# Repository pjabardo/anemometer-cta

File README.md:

# Project of a thermistor based constant temperature anemometer

This repository contains files related to a constant temperature anemometer that uses a self heated NTC thermistor as a sensing element.

## Thermal anemometer

An anemometer is a device that measures fluid speed, in particular air. A thermal anemometer uses heat transfer from a heated element to estimate the velocity of the fluid. There are several ways to build a thermal anemometer but the most common is the use of a self heated resistor whose resistance varies with temperature.

As a side note, a few years ago, José Pucci Caly, a professor at Mackenzie University in São Paulo/Brazil developed with a couple of students a very simple anemometer: the external temperature of the bulb from an incandescent light bulb was calibrated against wind speed. It worked. How well? I don't remember...

There are several ways that a self heated resistor can be used as the two mosto common aproaches are:

 * Constant temperature
 * Constant current

In this project we use the constant temperature approach.

## CTA - Constant temperature anemometer

The basic idea behind the constant temperature anemometer (CTA) is that an electric current passing through a resistor will heat the resistor. The temperature of the resistor is the result of the heat transfer to the fluid flowing around it.

Now suppose that for a given fluid velocity the temperature of the resistor is Tw. If the velocity then increases a tiny bit, Tw should drop a little bit. This drop in temperature corresponds to a change in resistance (when the resistance depends on the temperature). This change in resistance can be picked up and the current flowing through the resistor is changed accordingly.

The figure below shows the basic idea behind the anemometer. In this figure, Rw is the sensor. An imbalance of the Wheatsone bridge will cause a change of the current on the feedback loop. While this basic layout explains in general terms what is being done, it doesn't work. For one, most op amps can not provide sufficient current to the bridge. But there are other issues with this simple scheme.

This project uses an NTC thermistor (<https://en.wikipedia.org/wiki/Thermistor>) as a sensing element. In this case, an increase in temperature results in a decrease of resistance. This change can be drastic. For instance for a thermistor with a resistance of 5k at 25oC, at 180oC, the resistance can be 100 Ohms.

## Understanding the circuit

If the flow spead increases, the temperature will decrease and therefore the thermistor's resistance wqill increase and the voltage just before the sensor will increase and that will increase the output from the op amp so that it restores balance. To handle larger currents, the output of the op amp is connected to the base of an NPN transistor.

Even with the transistor in place, the circuit will not work. How does it start? When the power is turned on, there is no current on the bridge and therefore no imbalance and the base current is zero. So the circuit stays off indefinitely.

One possible solution is to nudge the + input of the op amp by connecting it to input voltage using a large resistor. This will work but now we have a problem: the operating point of the circuit will depend on the input voltage. This is not good. The figure below shows the basic circuit used:

This figure was generated from the text file  `cta-circuit.txt` using the online Falstad circuit simulator (<https://www.falstad.com/circuit/circuitjs.html>). Go to the previous link, select File -> Import from text and copy and paste the contents of the `cta-circuit.txt` file.

This is the completed circuit. The sub-circuit on the lower right hand side of the circuit basically unbalances the + input of op amp during power up so that the circuit is started. When the 10uF capacitor is charged, the PNP transistor is switched off and this branch of the circuit plays no role anymore.

There is now an input filter at the op amp. Without the feedback capacitor, once the bridge reached equilibrium, the current would be cutoff. The 100nF capacitor works as a integral controller.

The output of the anemometer is the voltage feeding the sensor. This output is fed to a voltage follower and then to a voltage divider to lower the voltage to levels adequate to an analog to digital converter and then there is another voltage follower to isolate the output.

This circuit uses 3 op amps and the LM324 quad 
## KiCad schematics

On the `kicad` folder is the KiCad project of the circuit.

## The finished board

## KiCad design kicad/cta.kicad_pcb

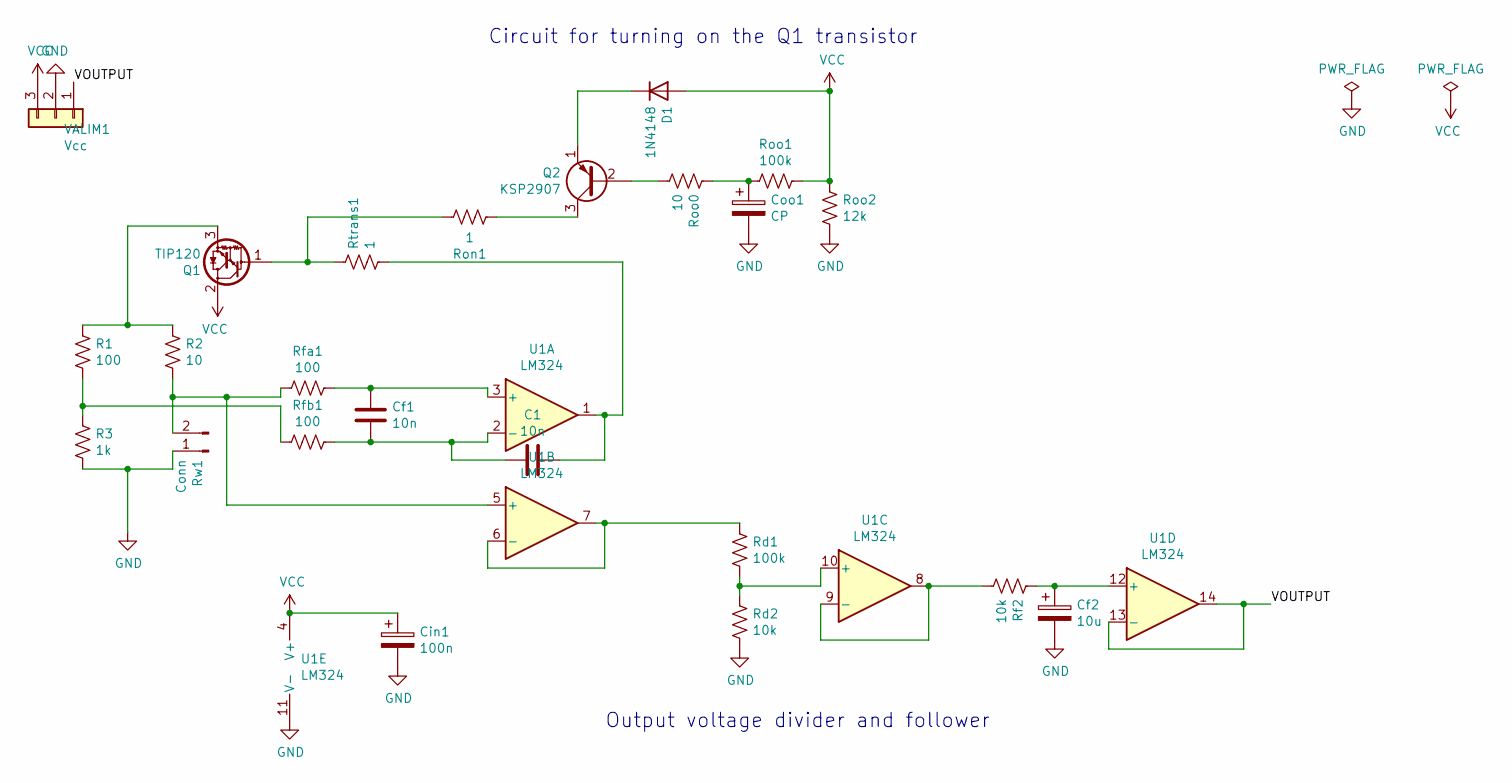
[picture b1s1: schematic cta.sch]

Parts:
C1: 10n; C_Rect_L7.2mm_W4.5mm_P5.00mm_FKS2_FKP2_MKS2_MKP2
Cf1: 10n; C_Rect_L7.2mm_W4.5mm_P5.00mm_FKS2_FKP2_MKS2_MKP2
Cf2: 10u; CP_Radial_D5.0mm_P2.50mm
Cin1: 100n; CP_Radial_D4.0mm_P2.00mm
Coo1: CP; CP_Radial_D5.0mm_P2.50mm
D1: 1N4148; D_DO-35_SOD27_P7.62mm_Horizontal
Q1: TIP120; TO-220-3_Vertical
Q2: KSP2907; TO-92_Inline_Wide
R1: 100; R_Axial_DIN0207_L6.3mm_D2.5mm_P10.16mm_Horizontal
R2: 10; R_Axial_Power_L20.0mm_W6.4mm_P22.40mm
R3: 1k; R_Axial_DIN0207_L6.3mm_D2.5mm_P10.16mm_Horizontal
Rd1: 100k; R_Axial_DIN0207_L6.3mm_D2.5mm_P10.16mm_Horizontal
Rd2: 10k; R_Axial_DIN0207_L6.3mm_D2.5mm_P10.16mm_Horizontal
Rf2: 10k; R_Axial_DIN0207_L6.3mm_D2.5mm_P10.16mm_Horizontal
Rfa1: 100; R_Axial_DIN0207_L6.3mm_D2.5mm_P10.16mm_Horizontal
Rfb1: 100; R_Axial_DIN0207_L6.3mm_D2.5mm_P10.16mm_Horizontal
Ron1: 1; R_Axial_DIN0207_L6.3mm_D2.5mm_P10.16mm_Horizontal
Roo0: 10; R_Axial_DIN0207_L6.3mm_D2.5mm_P10.16mm_Horizontal
Roo1: 100k; R_Axial_DIN0207_L6.3mm_D2.5mm_P10.16mm_Horizontal
Roo2: 12k; R_Axial_DIN0207_L6.3mm_D2.5mm_P10.16mm_Horizontal
Rtrans1: 1; R_Axial_DIN0207_L6.3mm_D2.5mm_P10.16mm_Horizontal
Rw1: Conn; TerminalBlock_bornier-2_P5.08mm
U1: LM324; DIP-14_W7.62mm_LongPads
VALIM1: Vcc; TerminalBlock_bornier-3_P5.08mm

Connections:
/VOUTPUT: U1.13 (-), U1.14, VALIM1.1
GND: Cf2.2, Cin1.2, Coo1.2, R3.2, Rd2.1, Roo2.2, Rw1.1, U1.11 (V-), VALIM1.2
unnamed: C1.1, Rtrans1.2, U1.1
unnamed: C1.2, Cf1.2, Rfb1.1, U1.2 (-)
unnamed: Cf1.1, Rfa1.1, U1.3 (+)
unnamed: Cf2.1, Rf2.1, U1.12 (+)
unnamed: Coo1.1, Roo0.1, Roo1.2
unnamed: D1.1 (K), Q2.1 (E)
unnamed: Q1.1 (B), Ron1.1, Rtrans1.1
unnamed: Q1.3 (E), R1.1, R2.1
unnamed: Q2.2 (B), Roo0.2
unnamed: Q2.3 (C), Ron1.2
unnamed: R1.2, R3.1, Rfb1.2
unnamed: R2.2, Rfa1.2, Rw1.2, U1.5 (+)
unnamed: Rd1.1, U1.6 (-), U1.7
unnamed: Rd1.2, Rd2.2, U1.10 (+)
unnamed: Rf2.2, U1.8, U1.9 (-)
VCC: Cin1.1, D1.2 (A), Q1.2 (C), Roo1.1, Roo2.1, U1.4 (V+), VALIM1.3

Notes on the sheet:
Circuit for turning on the Q1 transistor
Output voltage divider and follower

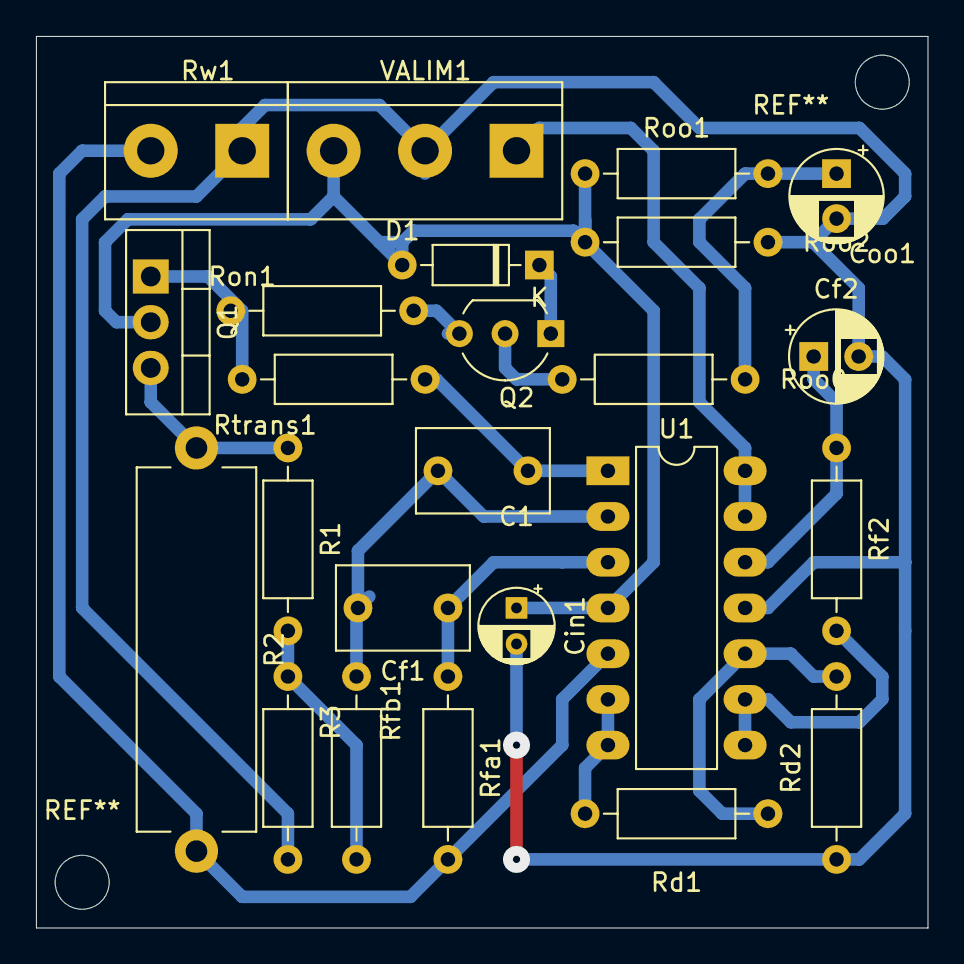
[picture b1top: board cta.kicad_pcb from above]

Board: 2 copper layers, 49.5 x 49.5 mm, 24 parts (0 on the bottom side), 18 nets.

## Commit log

2020-10-06 Initial commit of the anemometer-cta project.
    This project is an attempt to develop a constant temperature anemometer.
    This project uses KiCad.
2020-10-07 Working on the README.md file
    Explaining how the anemometer works.
2020-10-07 Set the right size for the cta-feedback.svg file.
2020-10-07 The README.md file explains the circuit
2020-10-21 Modified the warmup subcircuit
    To initialize the circuit, a subcircuit was used that on powerup would
    temporarily add voltage to the + leg of the op amp. Now this circuit adds
    this voltage directly to the base of Q1. With this I could also remove
    the resistor conecting both cricuits (Rs1).
    I also decreased the fill zones tolerances and most of the board is now
    filled.
2020-10-21 Updated the circuit code for the falstad circuit simulator.
    And the corresponding figure on the README.md file.
2020-10-25 Fixed a few things but there are several issues that I should fix
    It is very difficult to solder the transistors. I will change the footprint to To-92L wide.
    Another issue is that the board, as designed is 2 in by 2 in. But the copper
    boards that I usually find are 50 mm. I should set edge cut to that measure.
2020-10-25 Improved board layout and allowed for a power resistor.
2020-10-25 Removed a terminal block and increased the power termninal block to 3
    The circuit uses the same ground for power and signal. So I removed the signal terminal block and added another terminal to the power terminal block
2020-10-25 Forgot to add mounting holes
    Now I have to test this new board
2020-10-29 Set new values for components
    One of the things I noticed with the circuit is an asymmetry when increasing wind speed vs decreasing. When increasing, the response is fast. But when decreasing it is very low.
    This is to be expected: the electronics respond much faster than the cooling: the maximum colling rate happens when there is no current and therefore heat transfer within the thermistor is the slow p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
    To make response more symmetric, I increased the the resistors at the op amp input from 1k to 47k. This introduced a new problem: the capacitor would not charge fast enough for the initial charge sub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
2020-10-29 Replaced transistor KSP2222A for BC517
    The BC517 is a darlington transistor and the response of the anemometer is much faster (when increasing wind speed). Why would I care about that if I went to all the trouble to make the response more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
    It really depends on the objective. If I want to measure the mean speed in a turbulent flow, using the more symmetric response is better. But If I want to estimate wind gusts, the faster response tim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
2020-10-30 I found out the trouble: too much power dissipated on the tranistor
    During normal operation, the current is low and therefore the voltage at the top of the bridge is low and the transistor needs to reduce a lot of voltage and dissipate a lot of heat. After normal ope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
    I see 2 solutions:
    1. Replace the transistor
    2. Modify the resistors
    I think I will do #2 anyway and do #2.
2020-10-30 Replaced the transistor from BC517 to TIP120 and resistors on the bridge
    The resistors on the top of the bridge now have the same value as on the bottom of the bridge. This decreased the power dissipated in the transistor.
    The new transistor can also include a heat sink dependeing on application. The setup is working on the protoboard. I has been working for the last hour, voltage input can be decreased to 15V and the 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
2020-11-02 Cleaned up the schematics
    The circuit is much clearer! I have tested the circuit 24 hours and it is working. Now I have to test it on a wind tunnel and checkout how well it operates.
2020-11-04 Used the last op amp to implement an active low pass output filter
    I think this is the best strategy to get a symmetric behavior when heating or cooling. Just get a time constant larger than the corresponding cooling time constant.
2020-12-13 The circuit was not working with low noise, low offset op amp
    I removed the input filter and the cicrcuit works with precision op amps. Stilll need to test the circuit exhaustively.
2020-12-23 Added a decoupling capacitor to op amp and improved layout
    I don't know if this will help but it may reduce noise and improve performance when voltage input is noisy.
